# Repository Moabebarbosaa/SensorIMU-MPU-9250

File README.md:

# Sensor IMU-MPU-9250 (Técnicas de Prototipagem)

O MPU9250 é um chip que tem um acelerômetro de 3 eixos, um giroscópio de 3 eixos e magnetômetro (sensor de campo magnético), também de 3 eixos. Aliado ao sensor de pressão BMP280, que se caracteriza pelo baixo consumo de energia, você tem um módulo com 10DOF (Degrees of Freedom), tudo isso em uma minúscula placa.

### 📋Algumas aplicações que utilizam o sensor

* **Robótica -** com o giroscópio é possivel observar mudanças em rotações para ajudar a determinar a orientação. Robôs com rodas podem usar tais sensores para navegar, fazer giros precisos e manter sua posição.
* **Acelerômetro -** aceleração de um carro.
* **Bússula -** pode medir a direção da bússola, permitindo ao dispositivo saber sua orientação em relação ao norte magnético, semelhante ao funcionamento de uma bússola portátil.

📗 Nossa aplicação será um dispositivo para medir a aceleração de um carro e fazer a indicação de direção.

Objetivo: Ao analisar a variação da aceleração é possível identificar que o carro está em movimento e medir qual a aceleração como forma do motorista se orientar para excesso de velocidade. Além disso o disposito também indicará qual a direção que o motorista está percorrendo.

🧾 Alguns dos componentes que utilizaremos:

  ➡️ Microcontrolador Atmega 328p
  ➡️ Sensor IMU-MPU-9250
  ➡️ Display Oled

## 📌 Vídeo e todos os arquivos envolvidos no projeto
  * https://drive.google.com/drive/folders/1gVeTYRhP5gSUuyDoxihd5mW5vrwc_VHs?usp=sharing

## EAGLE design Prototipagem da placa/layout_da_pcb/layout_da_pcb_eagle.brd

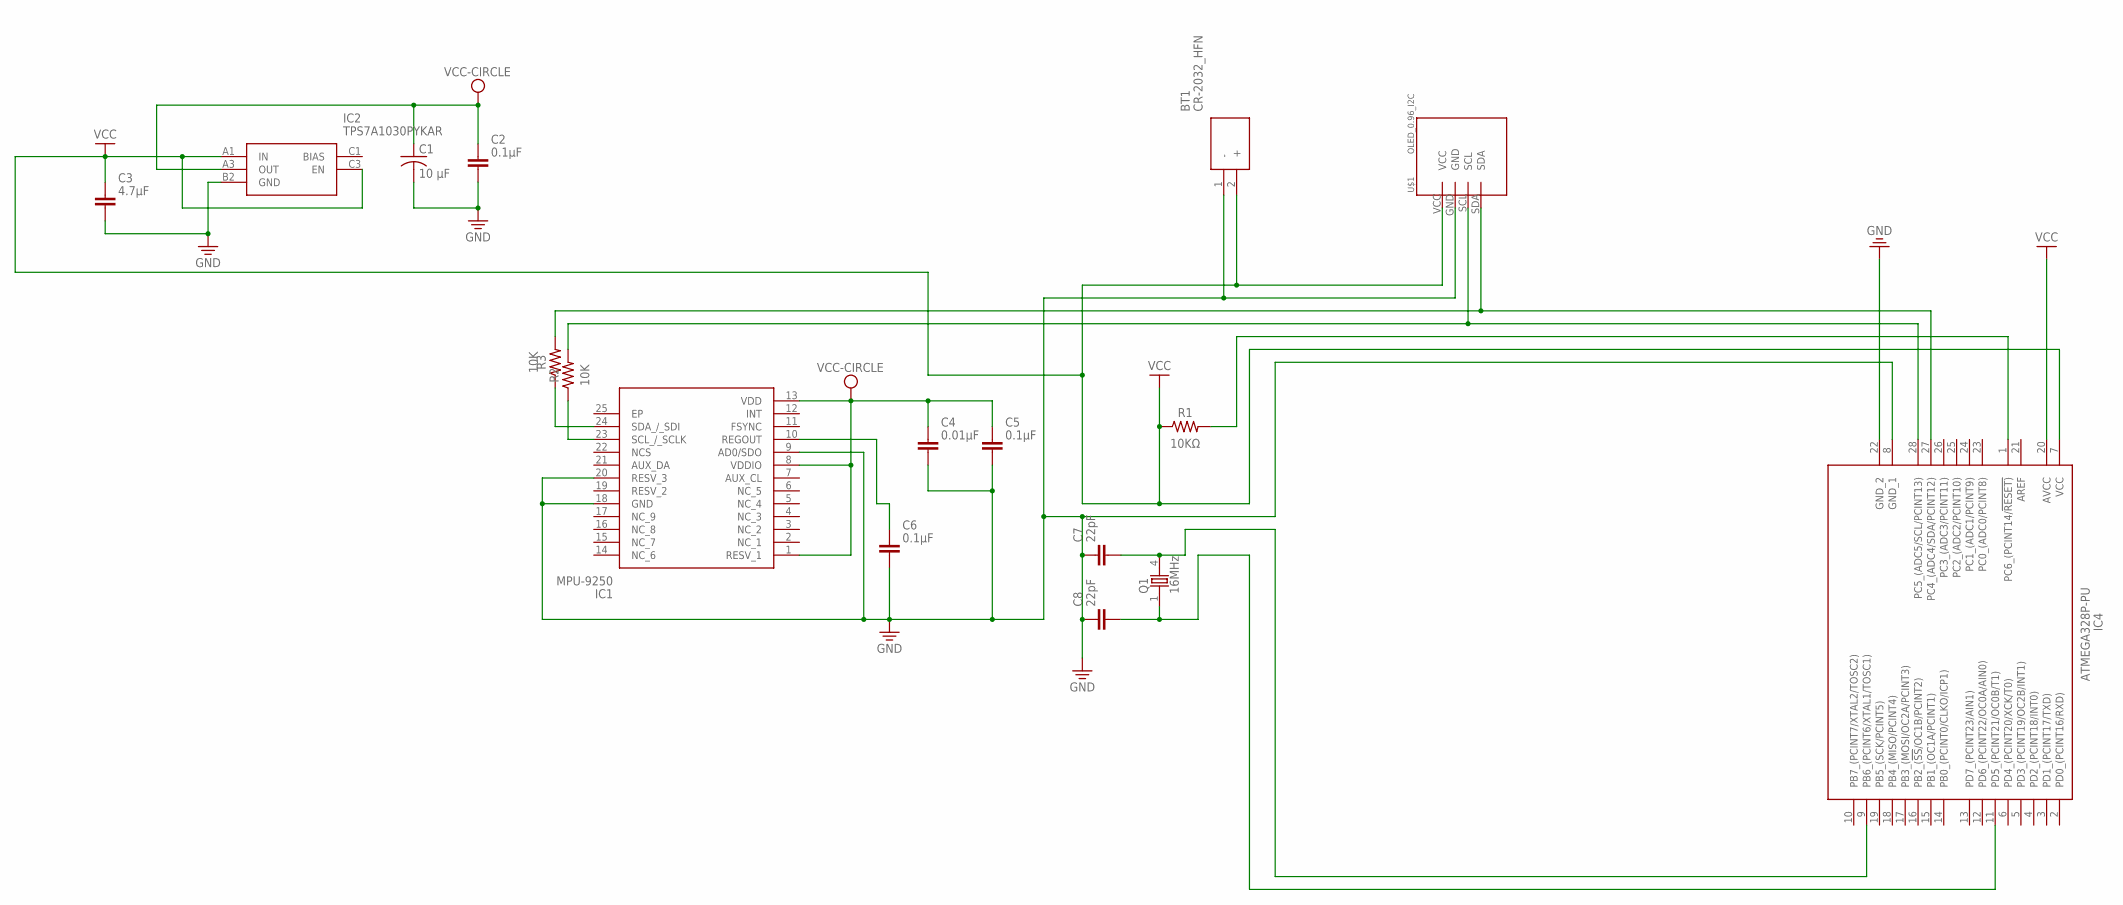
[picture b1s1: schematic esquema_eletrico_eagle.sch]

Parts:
BT1: CR-2032_HFN; CR-2032HFN
C1: 10 µF; CAPC1005X60
C2, C5, C6: 0.1µF; CAPC1005X60
C3: 4.7µF; CAPC1005X60
C4: 0.01µF; CAPC1005X60
C7, C8: 22pF; CAPC1005X60
IC1: MPU-9250; QFN40P300X300X105-25N
IC2: TPS7A1030PYKAR
IC4: ATMEGA328P-PU; DIP794W53P254L3467H457Q28N
Q1: 16MHz; 86SMX
R1: 10KΩ; RESC1608X60
R2, R3: 10K; RESAD724W46L381D178B
U$1: OLED_0.96_I2C

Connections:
GND: BT1.1 (-), C1.2, C2.2, C3.2, C4.2, C5.2, C6.2, C7.1, C8.1, IC1.9 (AD0/SDO), IC1.18 (GND), IC1.20 (RESV_3), IC2.B2 (GND), IC4.8 (GND_1), IC4.22 (GND_2), U$1.GND
unnamed: IC4.27 (PC4_(ADC4/SDA/PCINT12)), R3.2, U$1.SDA
unnamed: IC4.28 (PC5_(ADC5/SCL/PCINT13)), R2.2, U$1.SCL
unnamed: IC1.23 (SCL_/_SCLK), R2.1
unnamed: IC1.24 (SDA_/_SDI), R3.1
unnamed: C6.1, IC1.10 (REGOUT)
unnamed: IC4.1 (PC6_(PCINT14/!RESET)), R1.2
unnamed: C7.2, IC4.9 (PB6_(PCINT6/XTAL1/TOSC1)), Q1.4 (2)
unnamed: C8.2, IC4.11 (PD5_(PCINT21/OC0B/T1)), Q1.1
VCC: BT1.2 (+), C1.1, C2.1, C3.1, C4.1, C5.1, IC1.1 (RESV_1), IC1.8 (VDDIO), IC1.13 (VDD), IC2.A1 (IN), IC2.A3 (OUT), IC2.C3 (EN), IC4.7 (VCC), IC4.20 (AVCC), R1.1, U$1.VCC

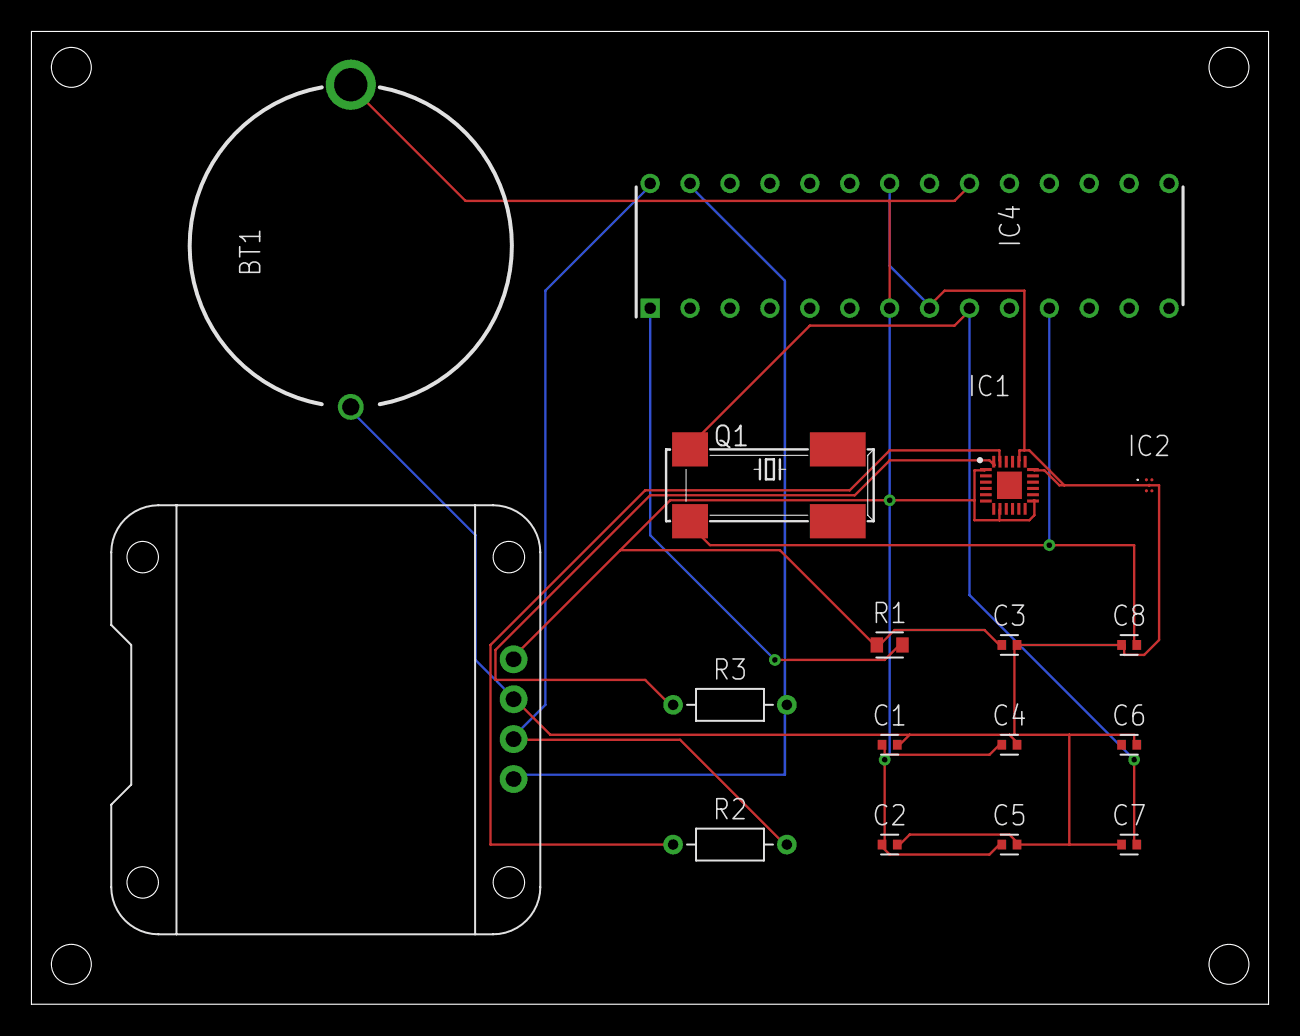
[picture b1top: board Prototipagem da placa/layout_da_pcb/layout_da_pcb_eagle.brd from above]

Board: 2 copper layers, 78.7 x 61.9 mm, 17 parts (0 on the bottom side), 10 nets.

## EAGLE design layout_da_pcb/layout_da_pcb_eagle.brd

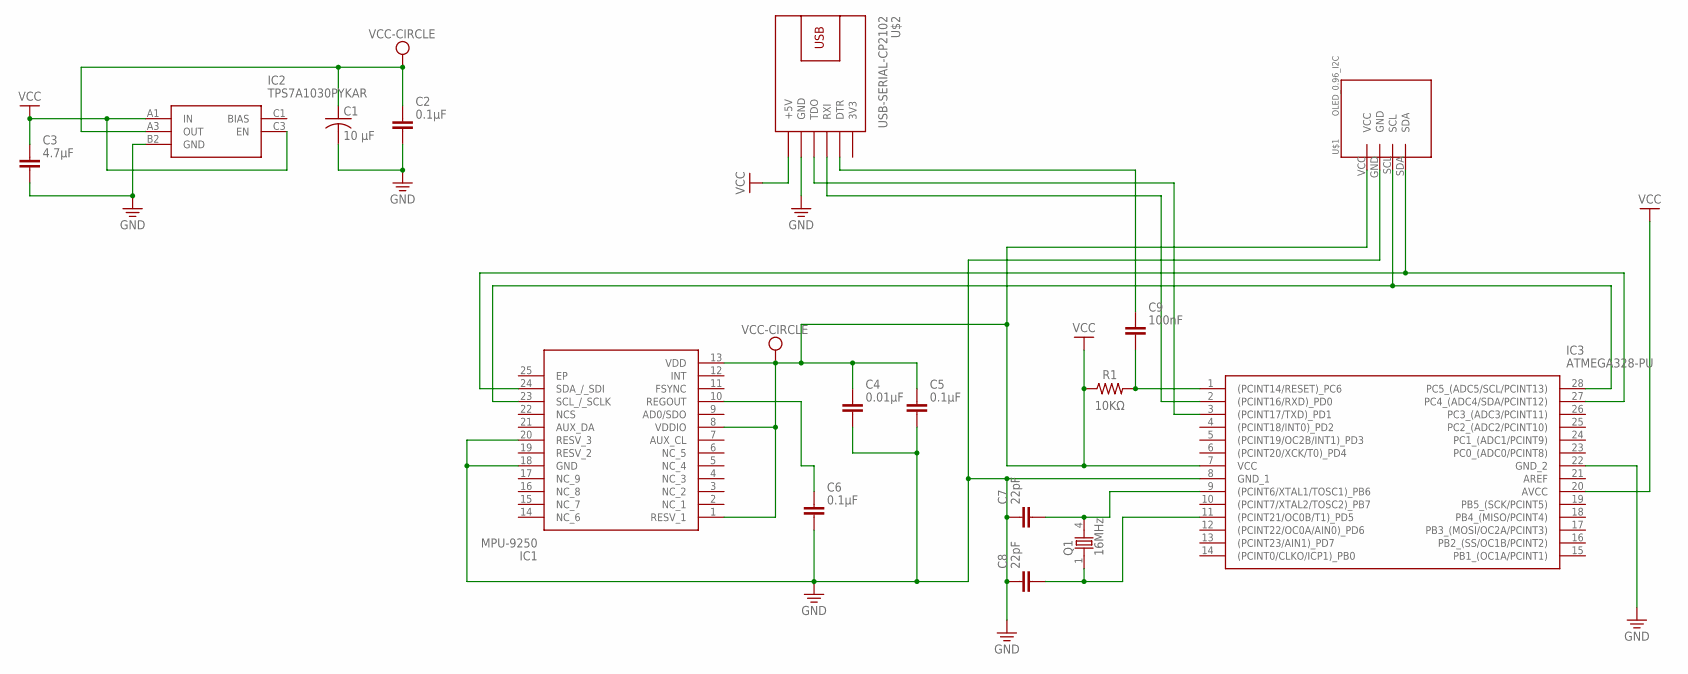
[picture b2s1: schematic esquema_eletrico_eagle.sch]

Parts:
C1: 10 µF; CAPC1005X60
C2, C5, C6: 0.1µF; CAPC1005X60
C3: 4.7µF; CAPC1005X60
C4: 0.01µF; CAPC1005X60
C7, C8: 22pF; CAPC1005X60
C9: 100nF; CAPC1005X60
IC1: MPU-9250; QFN40P300X300X105-25N
IC2: TPS7A1030PYKAR
IC3: ATMEGA328-PU; DIP1016W53P254L3468H457Q28N
Q1: 16MHz; 86SMX
R1: 10KΩ; RESC1608X60
U$1: OLED_0.96_I2C
U$2: USB-SERIAL-CP2102

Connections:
3V3: U$2.1 (3V3)
GND: C1.2, C2.2, C3.2, C4.2, C5.2, C6.2, C7.1, C8.1, IC1.18 (GND), IC1.20 (RESV_3), IC2.B2 (GND), IC3.8 (GND_1), IC3.22 (GND_2), U$1.GND, U$2.5 (GND)
unnamed: IC3.2 ((PCINT16/RXD)_PD0), U$2.3 (RXI)
unnamed: IC1.24 (SDA_/_SDI), IC3.27 (PC4_(ADC4/SDA/PCINT12)), U$1.SDA
unnamed: IC1.23 (SCL_/_SCLK), IC3.28 (PC5_(ADC5/SCL/PCINT13)), U$1.SCL
unnamed: IC3.3 ((PCINT17/TXD)_PD1), U$2.4 (TDO)
unnamed: C9.1, U$2.2 (DTR)
unnamed: C6.1, IC1.10 (REGOUT)
unnamed: C9.2, IC3.1 ((PCINT14/RESET)_PC6), R1.2
unnamed: C7.2, IC3.9 ((PCINT6/XTAL1/TOSC1)_PB6), Q1.4 (2)
unnamed: C8.2, IC3.11 ((PCINT21/OC0B/T1)_PD5), Q1.1
VCC: C1.1, C2.1, C3.1, C4.1, C5.1, IC1.1 (RESV_1), IC1.8 (VDDIO), IC1.13 (VDD), IC2.A1 (IN), IC2.A3 (OUT), IC2.C3 (EN), IC3.7 (VCC), IC3.20 (AVCC), R1.1, U$1.VCC, U$2.6 (+5V)

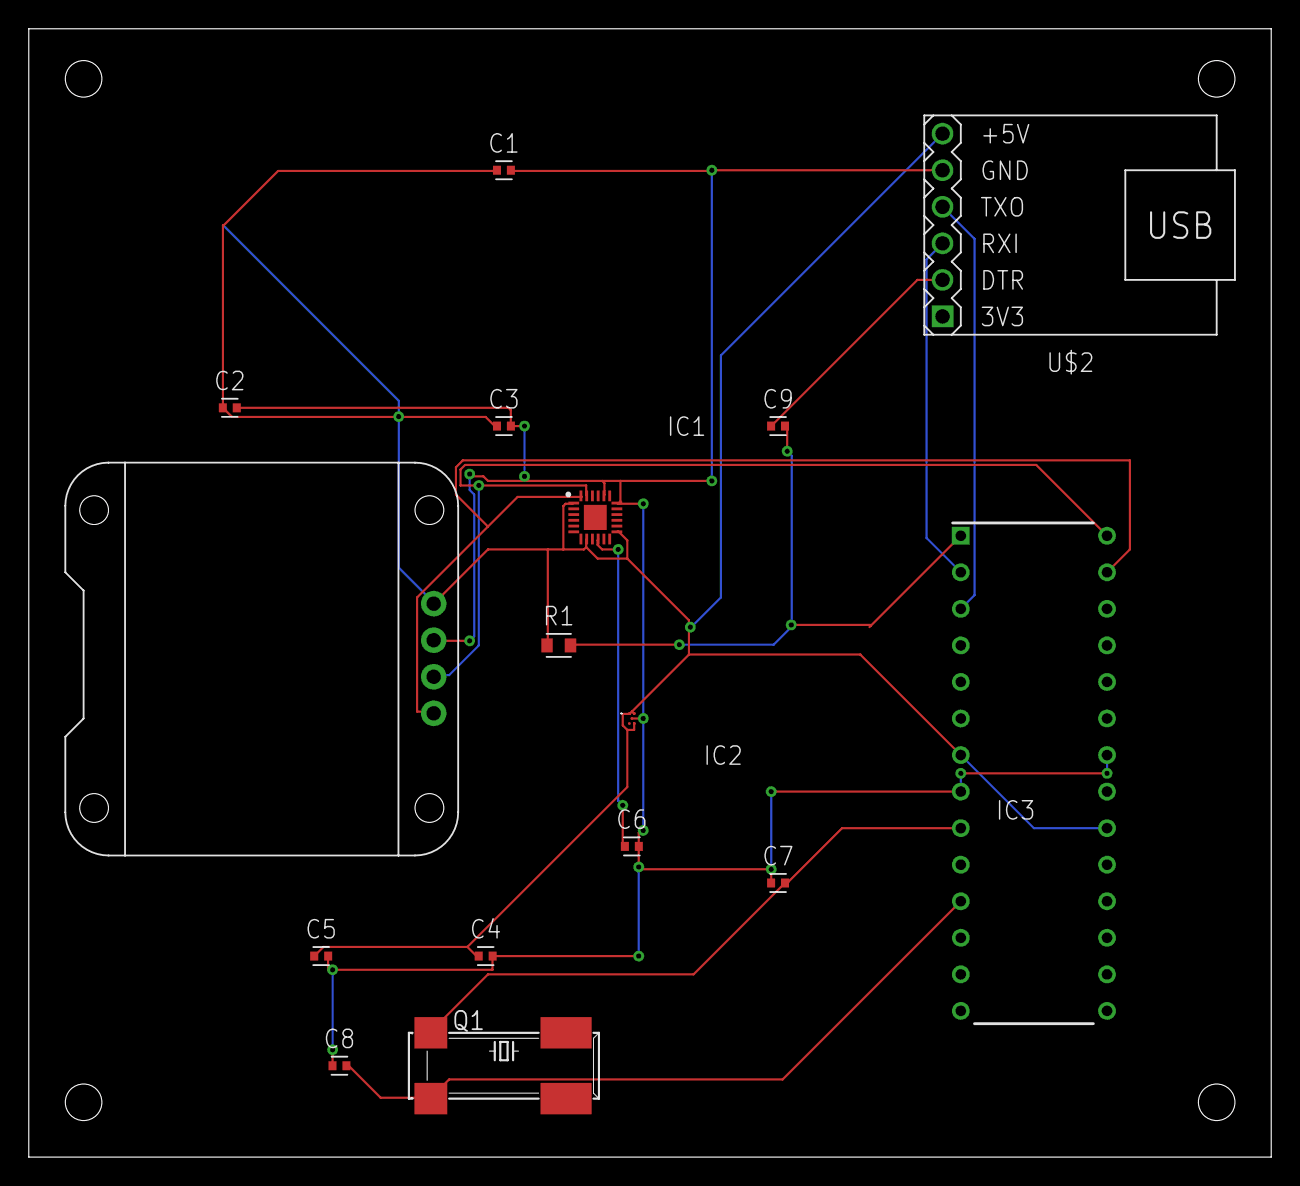
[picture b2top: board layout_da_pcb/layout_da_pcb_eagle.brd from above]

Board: 2 copper layers, 86.3 x 78.4 mm, 16 parts (0 on the bottom side), 11 nets.

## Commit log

2021-07-28 imagens
2021-09-09 Atualização do projeto
2021-10-10 finalização do projeto

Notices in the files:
parts and their libraries:
USB TO TTL: Released under the Creative Commons Attribution 4.0 International License: http://creativecommons.org/licenses/by/4.0
